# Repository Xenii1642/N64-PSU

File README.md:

<picture> <source media="(prefers-color-scheme: dark)" srcset="Images/logo-white.png" width="800">  </picture> 

# Introduction 
The N64-PSU is a simple, compact, cheap and open-source Nintendo 64 Power Supply Unit. 
It can be used to power trimmed Nintendo 64 motherboard, or builds like the [Matterhorn 64 Core](https://github.com/Xenii1642/Matterhorn-64-CORE/)
This board is based on the [CrazyGadget's PSU-PLUS](https://github.com/CrazyGadgetMods/PSU-Plus). 
Further information can be found on this [BitBuilt Post](https://bitbuilt.net/forums/threads/n64-psu-tiny-and-open-source-nintendo-64-psu.7408/)

# Caracteristics 
- Input voltage from 6V to 18V
- 3.3V Regulator
- 5V Regulator
- Up to 3A per rail
- 16x25mm form factor
- Price under $5 per unit 

# Ordering
The PCB Gerbers files are available in the [Gerbers folder](https://github.com/Xenii1642/N64-PSU/tree/main/Gerbers) of this repository. 
They can be ordered through either [PCBway](https://www.pcbway.com/), [JLCPCB](https://www.jlcpcb.com/) or the manufacturer you want. 

Components are listed in the [BOM.pdf](https://github.com/Xenii1642/N64-PSU/blob/main/BOM.pdf) file, and can be ordered through [Digikey](https://www.digikey.com/)

# Connection Diagram
The N64-PSU can be connected to a Nintendo 64 motherboard as shown:

⚠️ It is highly recommended to remove the original 12 to 5V LDO (U13) ⚠️

⚠️ Never power the console by both the original power supply and the N64-PSU as the same time.
This will damage and destroy the voltage regulators of the N64-PSU. ⚠️

For further information, please take a look at the [N64 Trimming Guide](https://bitbuilt.net/forums/threads/the-advanced-n64-trimming-guide.3992/) on [Bitbuilt.net](https://bitbuilt.net/forums/)

Any modified versions of derivatives must also remain open-source under the same, unmodified license.
You must also properly credit the original creators when reusing or redistributing these files.

# Support
If you notice anything wrong with this design, please let me know! 
You can also reach to me for questions or general help, I'm always happy to help 👍

Thank you for your support and see you next time!

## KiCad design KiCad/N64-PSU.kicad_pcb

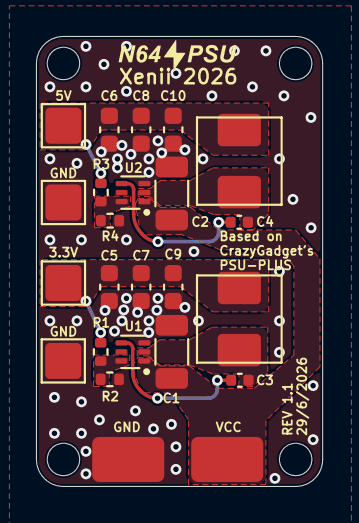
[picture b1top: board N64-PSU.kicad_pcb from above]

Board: 2 copper layers, 15.9 x 25.0 mm, 24 parts (0 on the bottom side), 10 nets.

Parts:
3.3V: 3v3; TestPoint_Pad_2.0x2.0mm
5V: 5v; TestPoint_Pad_2.0x2.0mm
C1, C2: 10uF; C_1206_3216Metric
C3, C4: 100nF; C_0402_1005Metric
C5, C6, C7, C8, C9, C10: 22uF; C_0603_1608Metric
GND: GND; TestPoint_Pad_2.0x2.0mm
GND#2: GND; TestPoint_Pad_2.0x2.0mm
L1, L2: 3.3uH; Coil
R1: 31.6kΩ; R_0402_1005Metric
R2, R4: 10kΩ; R_0402_1005Metric
R3: 52.3kΩ; R_0402_1005Metric
TP1: VCC; PowerPad
TP2: GND; PowerPad
U1, U2: AP62301Z6-7; AP62301Z6

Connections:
GND: C1.1, C2.1, C5.2, C6.2, C7.2, C8.2, C9.2, C10.2, GND.1, GND#2.1, R2.2, R4.2, TP2.1, U1.3 (GND), U2.3 (GND)
unnamed: 3.3V.1, C5.1, C7.1, C9.1, L1.2, R1.1
unnamed: 5V.1, C6.1, C8.1, C10.1, L2.2, R3.1
unnamed: C3.1, U1.4 (BST)
unnamed: R1.2, R2.1, U1.6 (FB)
unnamed: C3.2, L1.1, U1.2 (SW)
unnamed: C4.1, U2.4 (BST)
unnamed: R3.2, R4.1, U2.6 (FB)
unnamed: C4.2, L2.1, U2.2 (SW)
VCC: C1.2, C2.2, TP1.1, U1.1 (VIN), U2.1 (VIN)

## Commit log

2026-06-29 Create LICENSE
2026-06-29 Expand README with N64-PSU details and instructions
    Added detailed information about the N64-PSU, including characteristics, ordering instructions, connection diagrams, licensing, and support information.
2026-06-29 Fix image references and dimensions in README
    Updated image file extensions and dimensions in README.
2026-06-29 Update README with link and remove License section
    Updated references to CrazyGadget's PSU-PLUS with a hyperlink and removed the License section for clarity.
2026-06-29 Update LICENSE
